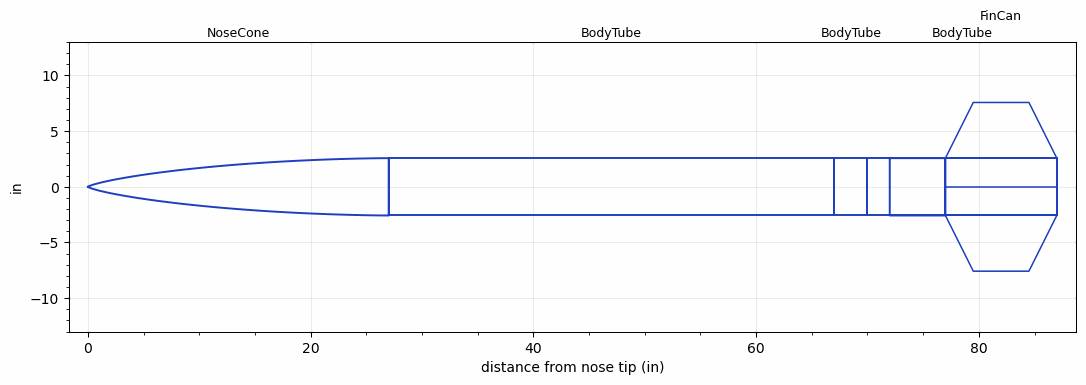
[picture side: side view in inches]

<RASAeroDocument>
 <FileVersion>2</FileVersion>
 <RocketDesign>
  <NoseCone>
   <Length>27</Length>
   <Diameter>5.15</Diameter>
   <Shape>LV-Haack</Shape>
   <Location>0</Location>
  </NoseCone>
  <BodyTube>
   <Length>40</Length>
   <Diameter>5.15</Diameter>
   <Location>27</Location>
  </BodyTube>
  <BodyTube>
   <Length>3</Length>
   <Diameter>5.15</Diameter>
   <Location>67</Location>
   <Protuberance>
    <StreamlinedNoBaseDrag>0</StreamlinedNoBaseDrag>
    <StreamlinedWithBaseDrag>0</StreamlinedWithBaseDrag>
    <InclinedPlate1Angle>90</InclinedPlate1Angle>
    <InclinedPlate1FrontalArea>3</InclinedPlate1FrontalArea>
    <InclinedPlate2Angle>0</InclinedPlate2Angle>
    <InclinedPlate2FrontalArea>0</InclinedPlate2FrontalArea>
   </Protuberance>
  </BodyTube>
  <BodyTube>
   <Length>17</Length>
   <Diameter>5.15</Diameter>
   <Location>70</Location>
  </BodyTube>
  <FinCan>
   <Length>10</Length>
   <Diameter>5.1501</Diameter>
   <InsideDiameter>5.15</InsideDiameter>
   <Location>87</Location>
   <ShoulderLength>5</ShoulderLength>
   <Offset>-10</Offset>
   <Fin>
    <Count>4</Count>
    <Chord>10</Chord>
    <Span>5</Span>
    <SweepDistance>2.5</SweepDistance>
    <TipChord>5</TipChord>
    <Thickness>0.1875</Thickness>
    <Location>10</Location>
    <AirfoilSection>Square</AirfoilSection>
   </Fin>
  </FinCan>
  <Surface>Smooth Paint</Surface>
  <ModifiedBarrowman>False</ModifiedBarrowman>
  <Turbulence>False</Turbulence>
  <UseBooster1>False</UseBooster1>
  <UseBooster2>False</UseBooster2>
 </RocketDesign>
 <LaunchSite>
  <Altitude>0</Altitude>
  <Pressure>0</Pressure>
  <RodAngle>0</RodAngle>
  <RodLength>4</RodLength>
  <Temperature>74</Temperature>
  <WindSpeed>0</WindSpeed>
 </LaunchSite>
 <Recovery>
  <Altitude1>1000</Altitude1>
  <Altitude2>1000</Altitude2>
  <DeviceType1>None</DeviceType1>
  <DeviceType2>None</DeviceType2>
  <Event1>False</Event1>
  <Event2>False</Event2>
  <Size1>1</Size1>
  <Size2>1</Size2>
  <EventType1>None</EventType1>
  <EventType2>None</EventType2>
  <CD1>1.33</CD1>
  <CD2>1.33</CD2>
 </Recovery>
</RASAeroDocument>
